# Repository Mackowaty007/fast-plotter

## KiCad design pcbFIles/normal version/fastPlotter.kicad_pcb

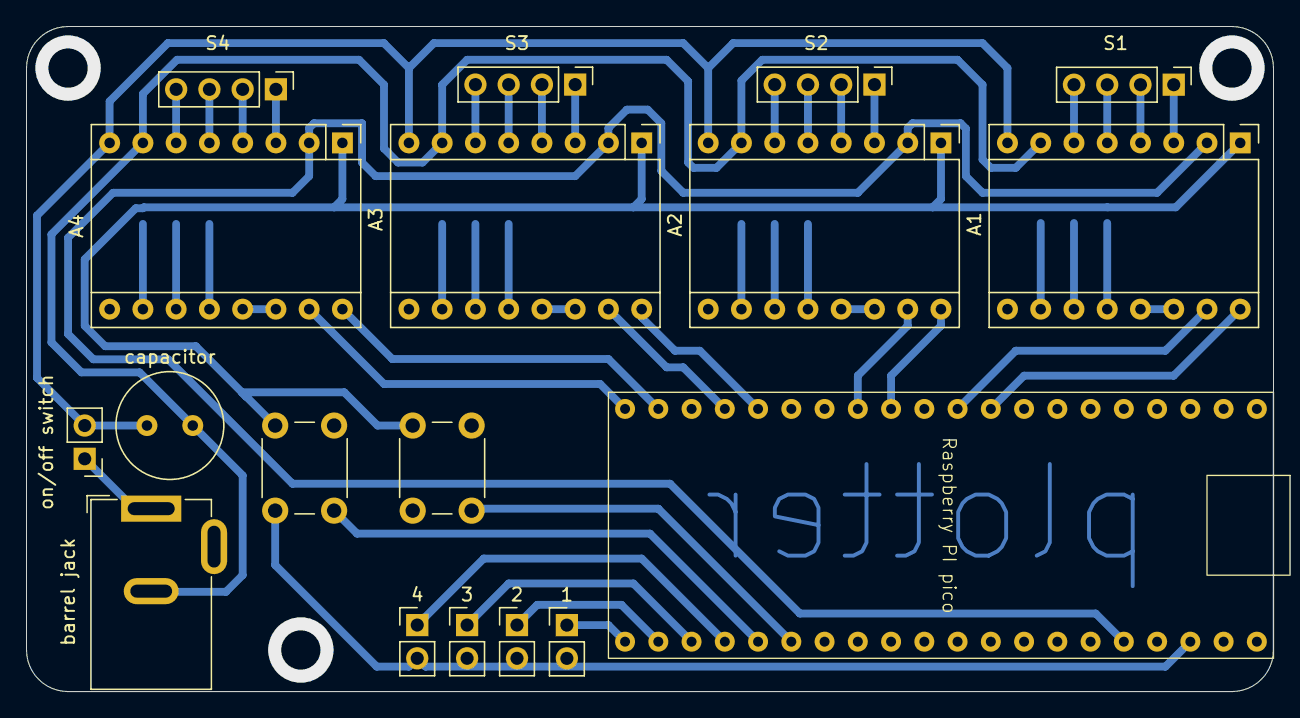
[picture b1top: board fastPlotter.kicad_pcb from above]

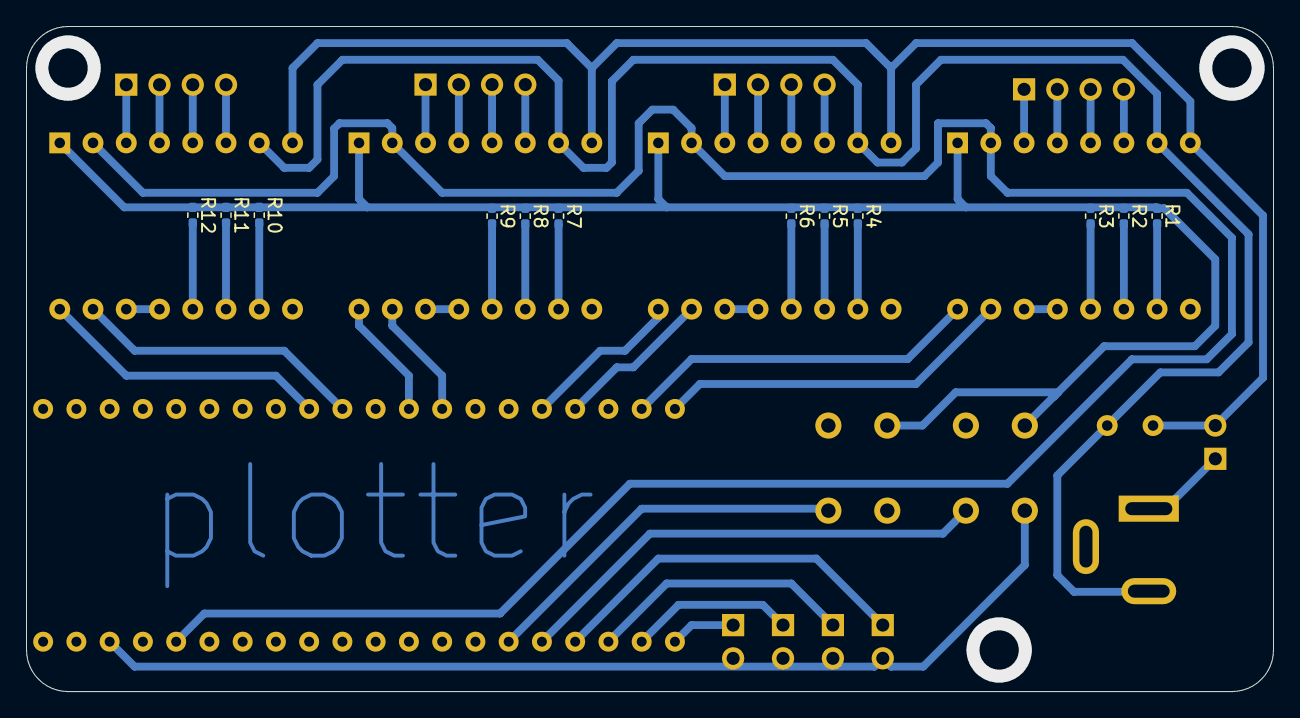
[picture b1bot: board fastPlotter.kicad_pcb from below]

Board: 2 copper layers, 95.3 x 50.8 mm, 30 parts (12 on the bottom side), 51 nets.

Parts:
1, 2, 3, 4: Conn_01x02_Socket; PinHeader_1x02_P2.54mm_Vertical
A1, A2, A3, A4: Pololu_Breakout_A4988; Pololu_Breakout-16_15.2x20.3mm
R1, R2, R3, R4, R5, R6, R7, R8, R9, R10, R11, R12: R; R_0402_1005Metric_Pad0.72x0.64mm_HandSolder
Raspberry PI pico: myRaspbrerryPiPicoNoTailPins
S1, S2, S3, S4: Conn_01x04_Socket; PinHeader_1x04_P2.54mm_Vertical
SW1, SW2: SW_Push; SW_PUSH_6mm
barrel jack: Barrel_Jack_MountingPin; BarrelJack_GCT_DCJ200-10-A_Horizontal
capacitor: C; C_Radial_D8.0mm_H7.0mm_P3.50mm
on/off switch: Conn_01x02_Socket; PinHeader_1x02_P2.54mm_Vertical

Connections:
unnamed: A1.4 (1A), S1.2
unnamed: A1.3 (1B), S1.1
unnamed: A1.5 (2A), S1.3
unnamed: A1.6 (2B), S1.4
unnamed: A1.16 (DIR), Raspberry PI pico.8 (7)
unnamed: A1.7 (GND), A2.7 (GND), A3.7 (GND), A4.7 (GND), barrel jack.2, capacitor.2
unnamed: A1.10 (MS1), R10.2
unnamed: A1.11 (MS2), R11.2
unnamed: A1.12 (MS3), R12.2
unnamed: A1.15 (STEP), Raspberry PI pico.9 (8)
unnamed: A1.2 (VDD), A2.2 (VDD), A3.2 (VDD), A4.2 (VDD), Raspberry PI pico.24 (3V3)
unnamed: A1.8 (VMOT), A2.8 (VMOT), A3.8 (VMOT), A4.8 (VMOT), capacitor.1, on/off switch.2
unnamed: A1.13 (~RESET), A1.14 (~SLEEP)
unnamed: A2.4 (1A), S2.2
unnamed: A2.3 (1B), S2.1
unnamed: A2.5 (2A), S2.3
unnamed: A2.6 (2B), S2.4
unnamed: A2.16 (DIR), Raspberry PI pico.11 (10)
unnamed: A2.10 (MS1), R7.2
unnamed: A2.11 (MS2), R8.2
unnamed: A2.12 (MS3), R9.2
unnamed: A2.15 (STEP), Raspberry PI pico.12 (11)
unnamed: A2.13 (~RESET), A2.14 (~SLEEP)
unnamed: A3.4 (1A), S3.2
unnamed: A3.3 (1B), S3.1
unnamed: A3.5 (2A), S3.3
unnamed: A3.6 (2B), S3.4
unnamed: A3.16 (DIR), Raspberry PI pico.15 (13)
unnamed: A3.10 (MS1), R4.2
unnamed: A3.11 (MS2), R5.2
unnamed: A3.12 (MS3), R6.2
unnamed: A3.15 (STEP), Raspberry PI pico.16 (14)
unnamed: A3.13 (~RESET), A3.14 (~SLEEP)
unnamed: A4.4 (1A), S4.2
unnamed: A4.3 (1B), S4.1
unnamed: A4.5 (2A), S4.3
unnamed: A4.6 (2B), S4.4
unnamed: A4.16 (DIR), Raspberry PI pico.18 (16)
unnamed: A4.10 (MS1), R1.2
unnamed: A4.11 (MS2), R2.2
unnamed: A4.12 (MS3), R3.2
unnamed: A4.15 (STEP), Raspberry PI pico.19 (17)
unnamed: A4.13 (~RESET), A4.14 (~SLEEP)
unnamed: barrel jack.1, on/off switch.1
unnamed: 4.1, Raspberry PI pico.36 (21)
unnamed: 3.1, Raspberry PI pico.37 (20)
unnamed: 2.1, Raspberry PI pico.38 (19)
unnamed: 1.1, Raspberry PI pico.39 (18)
unnamed: 1.2, 2.2, 3.2, 4.2, A1.1 (GND), A2.1 (GND), A3.1 (GND), A4.1 (GND), R1.1, R2.1, R3.1, R4.1, R5.1, R6.1, R7.1, R8.1, R9.1, R10.1, R11.1, R12.1, Raspberry PI pico.22 (GND), SW1.2, SW2.2
unnamed: Raspberry PI pico.35 (22), SW1.1
unnamed: Raspberry PI pico.34 (23), SW2.1
